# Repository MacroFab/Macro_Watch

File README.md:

***
###Macro_Watch
***
**Low cost, binary watch based off the PIC16F527 MCU for promotional purposes at MacroFab, INC.**

This repository contains all the documentation and instructions needed to build a Macro_Watch. The Macro_Watch is a binary style watch based off the [PIC16F527](http://ww1.microchip.com/downloads/en/DeviceDoc/41652A.pdf). It is designed to be low cost and easy to manufacture. The watch runs off of a single CR2032. The PIC16F527 is running in "LP" (Low Power Crystal Mode) which has an average power draw of ~15.8uA @ the 3.0V the watch runs at. The crystal is a 32.768kHz which allows for a clean conversion to a 1Hz signal for timekeeping. The Macro_Watch is designed to be mounted on an ESD wrist band. 

***
**How to assemble the Macro_Watch Kit**

To attach the wrist strap to the Macro_Watch follow the pictures below.

***
**Instructions on how to read and use the Macro_Watch**

The Macro_Watch has 11 LEDs. Four LEDs for the Hour (H1 - H4), Six LEDs for the Minute (M1 - M6), and a single Seconds LED for timing purposes. This guide will not go into how to read binary but a good guide can be found [here](http://www.wikihow.com/Read-Binary). Pressing the switch on the front will lit up the LEDs for 10 seconds to allow reading of the time. Holding the switch for 3 seconds will allow setting the current time. The time advances with acceleration so the longer the button is pressed the faster the time will increase. There is no AM/PM indicator on the watch. The SEC LED can be repurposed for AM/PM use or the user can look outside and see if the sun is out. 

The LEDs represent the following numbers. The Seconds LED (SEC on the PCB) blinks every second. 

**Table of the LED layout on the Macro_Watch**

| LED Identifier | Number | LED Identifier | Number
|---|---|---|---|
| N/A | N/A | M6 | 32 Minutes |
| H4 | 8 Hours | M5 | 16 Minutes |
| H3 | 4 Hours | M4 | 8 Minutes |
| H2 | 2 Hours | M3 | 4 Minutes |
| H1 | 1 Hour | M2 | 2 Minutes |
| SEC | Second Blinker | M1 | 1 Minute |

***

The idea is to take the LEDs that are lit up and then add up the numbers they represent. If H3 and H1 LED are lit up that will be 4 + 1 = 5 so it is the 5th hour. 

***
**Theory of operation**

The code works by using Timer0 on the PIC16F527 to time keep. Using a 32.768kHz oscillator and no timer prescaler (by setting the prescaler to work on the WDT instead of Timer0) the Timer0 ISR happens 32 times a second. The ISR counts 32 times and then adds one second to the current time. The pad labeled RA2 on the MacroWatch is high when ISR starts and goes low when the ISR finishes. 

The main loop of the code is a small state machine that keeps track what mode the watch is currently in. The first state is the idle state where the watch poles the switch and awaits the users input. Once the button is pressed it moves to the second state which is to calculate how long the watch will display for and then it moves on to state three. State three does the bulk of the work by branching based on how much time the display has been on for and what the user is currently doing. The watch is also driving the LEDs in this state. If the user has held the button for more then 3 seconds the watch goes into state four. State four advances the time. The longer the button is pressed the faster the time advances. Below is a state machine diagram showing how the code branches.

***
**License Information**

This project is under the [Creative Commons Attribution-ShareAlike 4.0 International License](LICENSE.md). This project is provided with no warranty and should be used at your own risk. 

***
**Directory listing of the repository**

| Directory | Description |
|---|---|
| Hardware | Contains all the hardware files for the Macro_Watch. Designed with Eagle V6.0+. | 
| Software | Has all the firmware that needs to be loaded onto the Macro_Watch. Written in C for MPLAB X IDE V3.10. |

***
**Credits**

Designed by:   
Parker Dillmann  

Software by:   
Parker Dillmann  

***

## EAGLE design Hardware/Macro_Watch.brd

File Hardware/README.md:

###Macro_Watch Hardware
***
**Low cost, binary watch based off the PIC16F527 MCU for promotional purposes at MacroFab, INC.**

***

***

Files are for Eagle V6.0+. Gerber files can be found in the camfiles directory. See main directory for licensing.

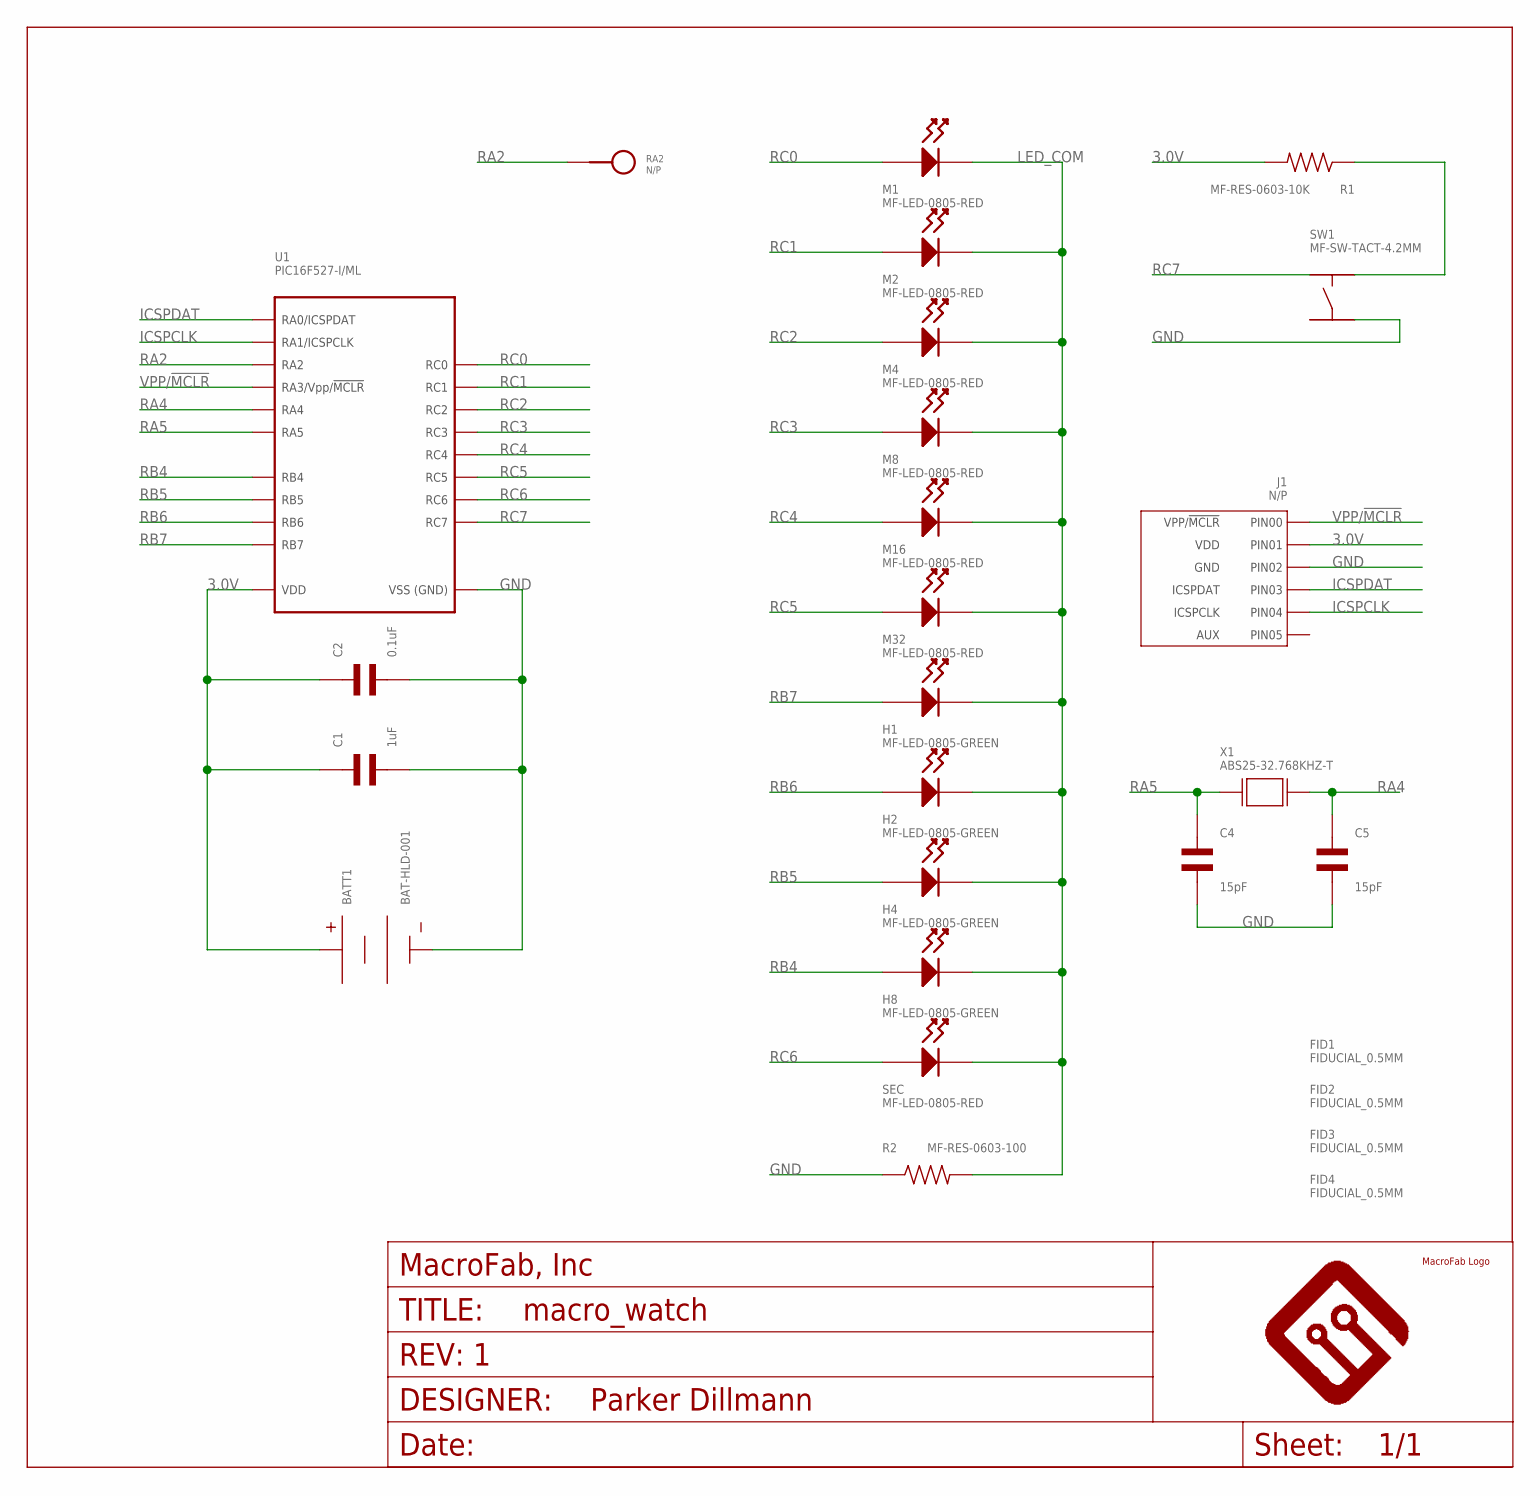
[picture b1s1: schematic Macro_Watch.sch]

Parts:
BATT1: BAT-HLD-001
C1: 1uF; C0603
C2: 0.1uF; C0603
C4, C5: 15pF; C0603
FID1, FID2, FID3, FID4: FIDUCIAL_0.5MM
FRAME1: MF_FRAMEDEFAULT; MF_FRAME_DEFAULT
H1, H2, H4, H8: MF-LED-0805-GREEN; LED0805
J1: N/P; PTH_2.54MM_01X06
M1, M2, M4, M8, M16, M32: MF-LED-0805-RED; LED0805
R1: MF-RES-0603-10K; R0603
R2: MF-RES-0603-100; R0603
RA2: N/P; ROUND_TP
SEC: MF-LED-0805-RED; LED0805
SW1: MF-SW-TACT-4.2MM; TACT4.2MM
U1: PIC16F527-I/ML; QFN20
U$1: MF_LOGOLOGO_SMALL; MF_LOGO_SMALL
X1: ABS25-32.768KHZ-T; ABS25_SERIES

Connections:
3.0V: BATT1.POS_0 (POS), BATT1.POS_1 (POS), C1.P$1, C2.P$1, J1.P$2 (PIN1), R1.P$2, U1.P$18 (VDD)
GND: BATT1.NEG_0 (NEG), C1.P$2, C2.P$2, C4.P$2, C5.P$2, J1.P$3 (PIN2), R2.P$1, SW1.P$4, U1.P$17 (GND)
ICSPCLK: J1.P$5 (PIN4), U1.P$15 (RA1/ICSPCLK)
ICSPDAT: J1.P$4 (PIN3), U1.P$16 (RA0/ICSPDAT)
LED_COM: H1.CATHODE, H2.CATHODE, H4.CATHODE, H8.CATHODE, M1.CATHODE, M2.CATHODE, M4.CATHODE, M8.CATHODE, M16.CATHODE, M32.CATHODE, R2.P$2, SEC.CATHODE
unnamed: R1.P$1, SW1.P$2
RA2: RA2.P$1, U1.P$14 (RA2)
RA4: C5.P$1, U1.P$20 (RA4), X1.4 (X1)
RA5: C4.P$1, U1.P$19 (RA5), X1.1 (X0)
RB4: H8.ANODE, U1.P$10 (RB4)
RB5: H4.ANODE, U1.P$9 (RB5)
RB6: H2.ANODE, U1.P$8 (RB6)
RB7: H1.ANODE, U1.P$7 (RB7)
RC0: M1.ANODE, U1.P$13 (RC0)
RC1: M2.ANODE, U1.P$12 (RC1)
RC2: M4.ANODE, U1.P$11 (RC2)
RC3: M8.ANODE, U1.P$4 (RC3)
RC4: M16.ANODE, U1.P$3 (RC4)
RC5: M32.ANODE, U1.P$2 (RC5)
RC6: SEC.ANODE, U1.P$5 (RC6)
RC7: SW1.P$1, U1.P$6 (RC7)
VPP/!MCLR: J1.P$1 (PIN0), U1.P$1 (RA3/VPP/!MCLR!)

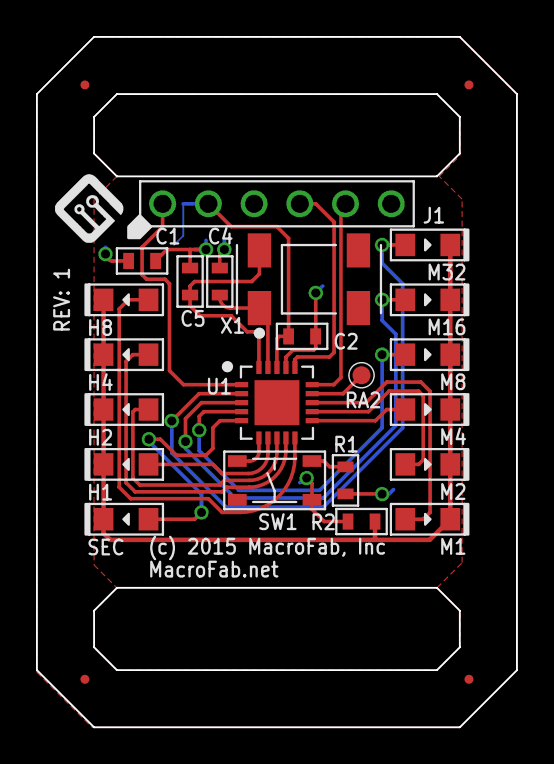
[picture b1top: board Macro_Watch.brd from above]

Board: 2 copper layers, 26.7 x 38.4 mm, 29 parts (1 on the bottom side), 22 nets.

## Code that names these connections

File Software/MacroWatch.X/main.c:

/*
 * File:   main.c
 * Author: Parker Dillmann
 *
 * Created on October 26, 2015, 4:07 PM
 */

#define _XTAL_FREQ 32768


// PIC16F527 Configuration Bit Settings

// 'C' source line config statements

#include <xc.h>

// #pragma config statements should precede project file includes.
// Use project enums instead of #define for ON and OFF.

// CONFIG
#pragma config FOSC = LP        // Oscillator Selection Interal
#pragma config WDTE = OFF       // Watchdog Timer Enable (WDT Disabled)
#pragma config CP = OFF         // Code Protection - User Program Memory (Code protection off)
#pragma config MCLRE = ON       // Master Clear Enable (MCLR pin functions as MCLR)
#pragma config IOSCFS = 8MHz    // Internal Oscillator Frequency Select (8 MHz INTOSC Speed)
#pragma config CPSW = OFF       // Code Protection - Self Writable Memory (Code protection off)
#pragma config BOREN = OFF      // Brown-out Reset Enable (BOR Enabled)
#pragma config DRTEN = OFF      // Device Reset Timer Enable (DRT Disabled)

#define HOURLED_0 RB7
#define HOURLED_1 RB6
#define HOURLED_2 RB5
#define HOURLED_3 RB4

#define MINLED_0  RC0
#define MINLED_1  RC1
#define MINLED_2  RC2
#define MINLED_3  RC3
#define MINLED_4  RC4
#define MINLED_5  RC5

#define SECOUT    RC6

#define SW        RC7

#define ISR       RA2

void TEST_LED_PATTERN(void);
void delay_ms(int);

char HOUR   = 3;
char MIN    = 6;
char SEC    = 0;
int INTCNT  = 0;

char Disp_timeout = 0;
char Change_time  = 0;
int  ADVCLKDELAY  = 0;      //How long till the minute counter is increased when changing the time.
int  ADVCLKCNT    = 0;      //How long till the value of the ADVCLKDELAY changes.

char BUTT_action = 0;

char STATE = 0;

void main(void) {
        
    CM1CON0 = 0x00; // These two registers must be zeroed out at the start to turn off comparators. 
    CM2CON0 = 0x00;
    OPTION = 0b11001000;
    ANSEL = 0x00;
    PORTA = 0x00;
    PORTB = 0x00;
    PORTC = 0x00;
    TRISA = 0x00;
    TRISB = 0x00;
    TRISC = 0x80;

    T0IE = 1;
    GIE=1;    
    
    TEST_LED_PATTERN();
        
    while (1)
    {
        switch(STATE)
        {
            //OFF STATE
            case 0:            
                PORTB = 0x00;
                PORTC = 0x00;
                
                if(SW == 0)
                {
                    STATE = 1;  
                    BUTT_action = 1;
                }
                else
                {
                    STATE = 0;
                    BUTT_action = 0;
                }
                break;
                
            //BUTTON PRESSED. RECORD TIME.
            case 1: 
                
                Disp_timeout = SEC; 
                Disp_timeout = Disp_timeout + 10;
                
                if(Disp_timeout >= 60)
                {
                    Disp_timeout = Disp_timeout - 60;
                }
                
                Change_time = SEC;
                Change_time = Change_time + 3; 
                
                if(Change_time >= 60)
                {
                    Change_time = Change_time - 60;
                }
                
                STATE = 2; 

                break;
            
            //TURN ON DISPLAY. AND WAIT FOR TIMEOUTS    
            case 2:
               
                HOURLED_0 = HOUR & 0b00000001;
                HOURLED_1 = (HOUR >> 1) & 0b00000001;
                HOURLED_2 = (HOUR >> 2) & 0b00000001;
                HOURLED_3 = (HOUR >> 3) & 0b00000001;
                
                MINLED_0  = MIN & 0b00000001; 
                MINLED_1  = (MIN >> 1) & 0b00000001; 
                MINLED_2  = (MIN >> 2) & 0b00000001;
                MINLED_3  = (MIN >> 3) & 0b00000001; 
                MINLED_4  = (MIN >> 4) & 0b00000001; 
                MINLED_5  = (MIN >> 5) & 0b00000001; 
                
                SECOUT    = SEC & 0b00000001; 
                
                
                //Display time out. Time to turn off display.
                if(Disp_timeout == SEC)
                {
                    STATE = 0;
                    BUTT_action == BUTT_action;
                }
                
                //Button is pressed again. Reset display time and set button action flag.
                else if(SW == 0 && BUTT_action == 0)
                {
                    STATE = 1;
                    BUTT_action = 1;
                }
                
                //Button is held for 3 seconds. Time to hack time!
                else if(Change_time == SEC && SW == 0 && BUTT_action == 1)
                {
                    STATE = 3;
                    BUTT_action == BUTT_action;
                    ADVCLKDELAY = 50;
                    ADVCLKCNT   = 2;
                }
                //Button has stopped being pressed. Clear button action flag.
                else if(SW == 1 && BUTT_action == 1)
                {
                    STATE = 2;
                    BUTT_action = 0; 
                }
                
                break;
              
            //INCREASE TIME AND DISPLAY TIME.    
            case 3:
                GIE = 0;
                
                //Switch held. Increase time.
                if(SW == 0)
                {
                    SEC = 0;
                    MIN = MIN + 1;
                    if(MIN == 60)
                    {
                        MIN = 0;
                        HOUR = HOUR + 1;
                        if(HOUR == 13)
                        {
                            HOUR = 1;   
                        }   
                    }
                    //Calculate "acceleration" of time hacking. 
                    ADVCLKCNT = ADVCLKCNT - 1;
                    if(ADVCLKCNT == 0 && ADVCLKDELAY > 5)
                    {
                        ADVCLKCNT = 3;
                        ADVCLKDELAY = ADVCLKDELAY - 5;
                    }
                   
                }    
                //Switch released. Recalculate on time. 
                else if(SW == 1)
                {
                    GIE = 1;
                    STATE = 1;
                }
                
                HOURLED_0 = HOUR & 0b00000001;
                HOURLED_1 = (HOUR >> 1) & 0b00000001;
                HOURLED_2 = (HOUR >> 2) & 0b00000001;
                HOURLED_3 = (HOUR >> 3) & 0b00000001;
                
                MINLED_0  = MIN & 0b00000001; 
                MINLED_1  = (MIN >> 1) & 0b00000001; 
                MINLED_2  = (MIN >> 2) & 0b00000001;
                MINLED_3  = (MIN >> 3) & 0b00000001; 
                MINLED_4  = (MIN >> 4) & 0b00000001; 
                MINLED_5  = (MIN >> 5) & 0b00000001; 
                
                delay_ms(ADVCLKDELAY);

                break;
            
                
            //Never supposed to get here but just encase of cosmic radiation flipping a bit.
            default:
                
                STATE = 0;
                
                break;   
        }

                
    }
    return;
}

void TEST_LED_PATTERN(void)
{
    GIE = 0;
    char mask = 0x01;
    
    for(int i = 0; i < 8; i++)
    {
        PORTB = mask;
        PORTC = mask;
        mask = mask << 1;
        __delay_ms(500);
    }
    GIE = 1;
    return;
}
 
void delay_ms(int milliseconds)
 {
   while(milliseconds > 0)
   {
       __delay_ms(10);
      milliseconds--;
    }
 }

void interrupt isr(void)
{
    ISR = 1;
    INTCNT = INTCNT + 1;
    if(INTCNT == 32)
    {  
        INTCNT = 0; 
        SEC = SEC + 1;
        
        if (SEC == 60)
        {
            SEC = 0;
            MIN = MIN + 1;
            if (MIN == 60)
            {
                MIN = 0;
                HOUR = HOUR + 1;
                if(HOUR == 13)
                {
                    HOUR = 1;
                } 
            } 
        }
    }
    ISR = 0;
    T0IF = 0;
    return;
}

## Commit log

2015-10-28 First push of hardware.
2015-10-28 Tweaked back side silkscreen
2015-10-29 Uploading instruction card pdf
2015-10-30 Added working camfiles and tweaked layout.
    Added a TP for RA2 pin on MCU. Gerber files have been checked and are
    ready for production.
2015-10-30 working on the README.md
2015-10-30 Adding Instructions on Reading the Watch.
2015-10-30 Gotta close the **
2015-10-30 derp need a /n
2015-10-30 Resize images?
2015-10-30 Testing image resizing.
2015-10-30 Instructions finished.
2015-10-30 Finished the instructions on how to read the watch.
2015-10-30 Hardware README.md added.
2015-10-30 Updated images.
2015-10-30 Adding Gerber image.
2015-11-03 Added code. Beta software.
2015-11-09 Finished release code.
2015-11-13 Updating pictures and README with documentation.
2015-11-13 Added Assembly Pictures.
2015-12-14 Updated TP to latest Library Style.
2016-02-12 Adding more EDA Tool support.
2016-08-10 updating readme

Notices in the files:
parts and their libraries:
MF_Aesthetics: (c) 2015 MacroFab, Inc
